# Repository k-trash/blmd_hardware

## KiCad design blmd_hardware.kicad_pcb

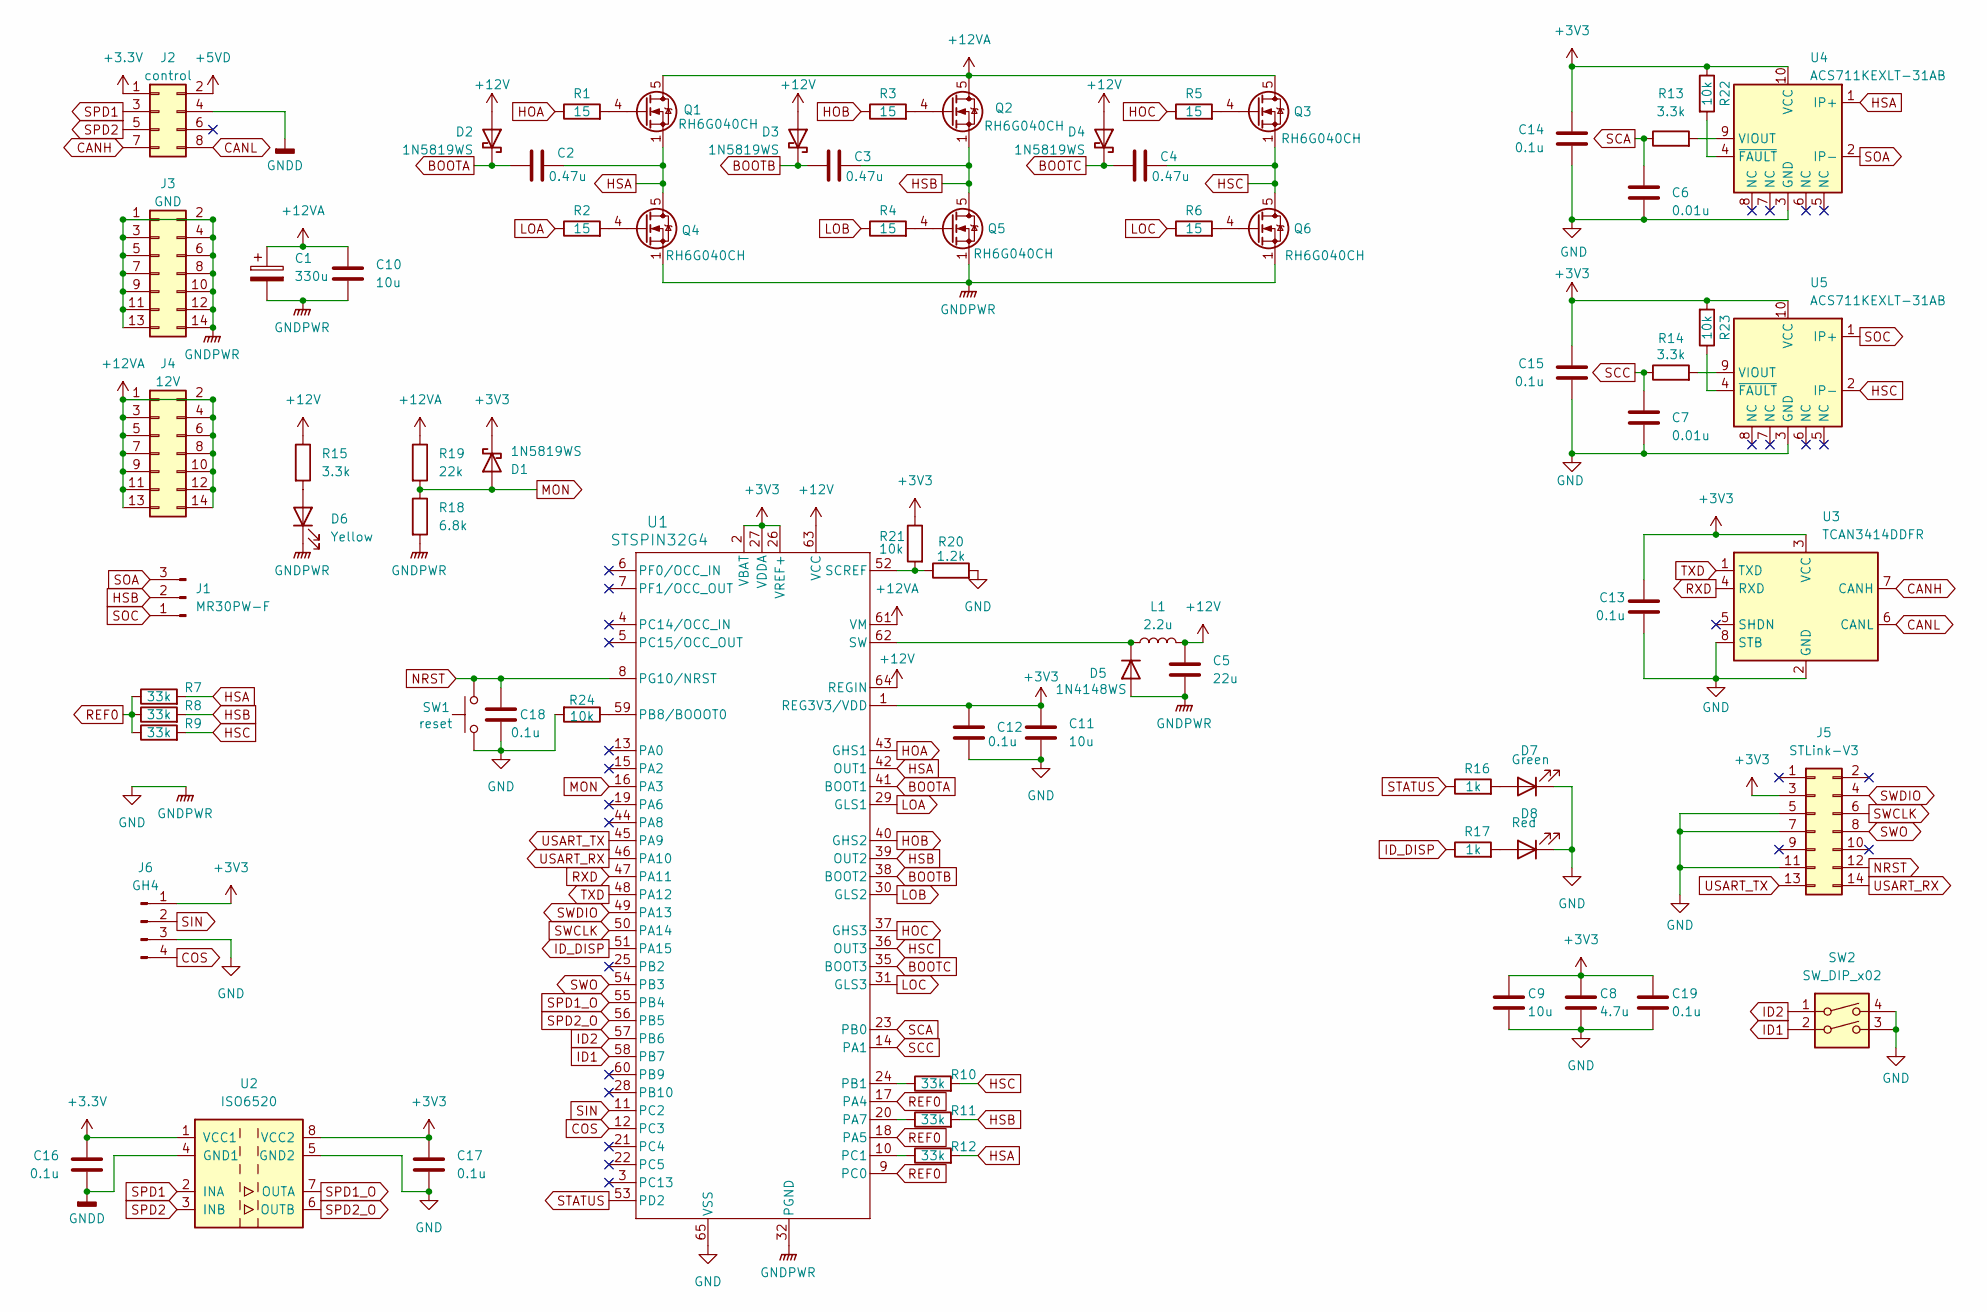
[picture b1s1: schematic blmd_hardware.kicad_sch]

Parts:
C1: 330u; CP_Radial_D10.0mm_P5.00mm
C2, C3, C4: 0.47u; C_0603_1608Metric_Pad1.08x0.95mm_HandSolder
C5: 22u; C_0805_2012Metric_Pad1.18x1.45mm_HandSolder
C6, C7: 0.01u; C_0603_1608Metric_Pad1.08x0.95mm_HandSolder
C8: 4.7u; C_0603_1608Metric_Pad1.08x0.95mm_HandSolder
C9, C10, C11: 10u; C_0603_1608Metric_Pad1.08x0.95mm_HandSolder
C12, C13, C14, C15, C16, C17, C18, C19: 0.1u; C_0603_1608Metric_Pad1.08x0.95mm_HandSolder
D1, D2, D3, D4: 1N5819WS; D_SOD-323_HandSoldering
D5: 1N4148WS; D_SOD-323_HandSoldering
D6: Yellow; LED_0603_1608Metric_Pad1.05x0.95mm_HandSolder
D7: Green; LED_0603_1608Metric_Pad1.05x0.95mm_HandSolder
D8: Red; LED_0603_1608Metric_Pad1.05x0.95mm_HandSolder
J1: MR30PW-F; AMASS_MR30PW-FB_1x03_P3.50mm_Horizontal
J2: control; PinHeader_2x04_P2.54mm_Horizontal
J3: GND; PinHeader_2x07_P2.54mm_Horizontal
J4: 12V; PinHeader_2x07_P2.54mm_Horizontal
J5: STLink-V3; CONN_3220-14-0300-00_CNC
J6: GH4; JST_GH_SM04B-GHS-TB_1x04-1MP_P1.25mm_Horizontal
L1: 2.2u; L_0603_1608Metric_Pad1.05x0.95mm_HandSolder
Q1, Q2, Q3, Q4, Q5, Q6: RH6G040CH; HSMT8
R1, R2, R3, R4, R5, R6: 15; R_0603_1608Metric_Pad0.98x0.95mm_HandSolder
R7, R8, R9, R10, R11, R12: 33k; R_0603_1608Metric_Pad0.98x0.95mm_HandSolder
R13, R14, R15: 3.3k; R_0603_1608Metric_Pad0.98x0.95mm_HandSolder
R16, R17: 1k; R_0603_1608Metric_Pad0.98x0.95mm_HandSolder
R18: 6.8k; R_0603_1608Metric_Pad0.98x0.95mm_HandSolder
R19: 22k; R_0603_1608Metric_Pad0.98x0.95mm_HandSolder
R20: 1.2k; R_0603_1608Metric_Pad0.98x0.95mm_HandSolder
R21, R22, R23, R24: 10k; R_0603_1608Metric_Pad0.98x0.95mm_HandSolder
SW1: reset; RESET
SW2: SW_DIP_x02; SW_DIP_SPSTx02_Slide_Copal_CHS-02B_W7.62mm_P1.27mm
U1: STSPIN32G4; QFN_IN32G4_STM
U2: ISO6520; SOIC-8_3.9x4.9mm_P1.27mm
U3: TCAN3414DDFR; SOT-23-8
U4, U5: ACS711KEXLT-31AB; Allegro_QFN-12-10-1EP_3x3mm_P0.5mm

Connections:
+3.3V: C16.1, J2.1, U2.1 (VCC1)
+3V3: C8.1, C9.1, C11.1, C12.1, C13.1, C14.1, C15.1, C17.1, C19.1, D1.1 (K), J5.3, J6.1, R21.1, R22.1, R23.2, U1.1 (REG3V3/VDD), U1.2 (VBAT), U1.26 (VREF+), U1.27 (VDDA), U2.8 (VCC2), U3.3 (VCC), U4.10 (VCC), U5.10 (VCC)
+5VD: J2.2
+12V: C5.1, D2.2 (A), D3.2 (A), D4.2 (A), L1.2, R15.1, U1.63 (VCC), U1.64 (REGIN)
+12VA: C1.1, C10.1, J4.1, J4.2, J4.3, J4.4, J4.5, J4.6, J4.7, J4.8, J4.9, J4.10, J4.11, J4.12, J4.13, J4.14, Q1.5 (D), Q1.6 (D), Q1.7 (D), Q1.8 (D), Q2.5 (D), Q2.6 (D), Q2.7 (D), Q2.8 (D), Q3.5 (D), Q3.6 (D), Q3.7 (D), Q3.8 (D), R19.1, U1.61 (VM)
BOOTA: C2.2, D2.1 (K), U1.41 (BOOT1)
BOOTB: C3.1, D3.1 (K), U1.38 (BOOT2)
BOOTC: C4.1, D4.1 (K), U1.35 (BOOT3)
CANH: J2.7, U3.7 (CANH)
CANL: J2.8, U3.6 (CANL)
COS: J6.4, U1.12 (PC3)
GND: C1.2, C5.2, C6.2, C7.2, C8.2, C9.2, C10.2, C11.2, C12.2, C13.2, C14.2, C15.2, C17.2, C18.2, C19.2, D5.2 (A), D6.1 (K), D7.1 (K), D8.1 (K), J3.1, J3.2, J3.3, J3.4, J3.5, J3.6, J3.7, J3.8, J3.9, J3.10, J3.11, J3.12, J3.13, J3.14, J5.5, J5.7, J5.11, J6.3, Q4.1 (S), Q4.2 (S), Q4.3 (S), Q5.1 (S), Q5.2 (S), Q5.3 (S), Q6.1 (S), Q6.2 (S), Q6.3 (S), R18.2, R20.2, R24.2, SW1.1, SW2.3, SW2.4, U1.32 (PGND), U1.65 (VSS), U2.5 (GND2), U3.2 (GND), U3.8 (STB), U4.3 (GND), U5.3 (GND)
GNDD: C16.2, J2.4, U2.4 (GND1)
HOA: R1.1, U1.43 (GHS1)
HOB: R3.1, U1.40 (GHS2)
HOC: R5.1, U1.37 (GHS3)
HSA: C2.1, Q1.1 (S), Q1.2 (S), Q1.3 (S), Q4.5 (D), Q4.6 (D), Q4.7 (D), Q4.8 (D), R7.2, R12.2, U1.42 (OUT1), U4.1 (IP+)
HSB: C3.2, J1.2, Q2.1 (S), Q2.2 (S), Q2.3 (S), Q5.5 (D), Q5.6 (D), Q5.7 (D), Q5.8 (D), R8.2, R11.2, U1.39 (OUT2)
HSC: C4.2, Q3.1 (S), Q3.2 (S), Q3.3 (S), Q6.5 (D), Q6.6 (D), Q6.7 (D), Q6.8 (D), R9.2, R10.2, U1.36 (OUT3), U5.2 (IP-)
ID1: SW2.2, U1.58 (PB7)
ID2: SW2.1, U1.57 (PB6)
ID_DISP: R17.1, U1.51 (PA15)
LOA: R2.1, U1.29 (GLS1)
LOB: R4.1, U1.30 (GLS2)
LOC: R6.1, U1.31 (GLS3)
MON: D1.2 (A), R18.1, R19.2, U1.16 (PA3)
NRST: C18.1, J5.12, SW1.2, U1.8 (PG10/NRST)
unnamed: D5.1 (K), L1.1, U1.62 (SW)
unnamed: D6.2 (A), R15.2
unnamed: D7.2 (A), R16.2
unnamed: D8.2 (A), R17.2
unnamed: Q1.4 (G), R1.2
unnamed: Q2.4 (G), R3.2
unnamed: Q3.4 (G), R5.2
unnamed: Q4.4 (G), R2.2
unnamed: Q5.4 (G), R4.2
unnamed: Q6.4 (G), R6.2
unnamed: R11.1, U1.20 (PA7)
unnamed: R10.1, U1.24 (PB1)
unnamed: R24.1, U1.59 (PB8/BOOOT0)
unnamed: R12.1, U1.10 (PC1)
unnamed: R20.1, R21.2, U1.52 (SCREF)
unnamed: R13.2, U4.9 (VIOUT)
unnamed: R22.2, U4.4 (~FAULT)
unnamed: R14.2, U5.9 (VIOUT)
unnamed: R23.1, U5.4 (~FAULT)
REF0: R7.1, R8.1, R9.1, U1.9 (PC0), U1.17 (PA4), U1.18 (PA5)
RXD: U1.47 (PA11), U3.4 (RXD)
SCA: C6.1, R13.1, U1.23 (PB0)
SCC: C7.1, R14.1, U1.14 (PA1)
SIN: J6.2, U1.11 (PC2)
SOA: J1.3, U4.2 (IP-)
SOC: J1.1, U5.1 (IP+)
SPD1: J2.3, U2.2 (INA)
SPD1_O: U1.55 (PB4), U2.7 (OUTA)
SPD2: J2.5, U2.3 (INB)
SPD2_O: U1.56 (PB5), U2.6 (OUTB)
STATUS: R16.1, U1.53 (PD2)
SWCLK: J5.6, U1.50 (PA14)
SWDIO: J5.4, U1.49 (PA13)
SWO: J5.8, U1.54 (PB3)
TXD: U1.48 (PA12), U3.1 (TXD)
USART_RX: J5.14, U1.46 (PA10)
USART_TX: J5.13, U1.45 (PA9)

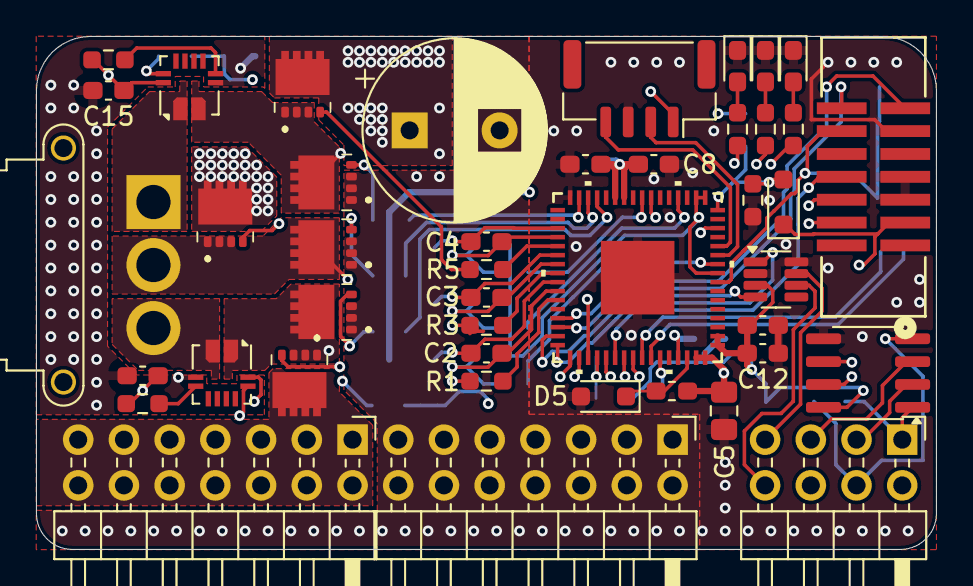
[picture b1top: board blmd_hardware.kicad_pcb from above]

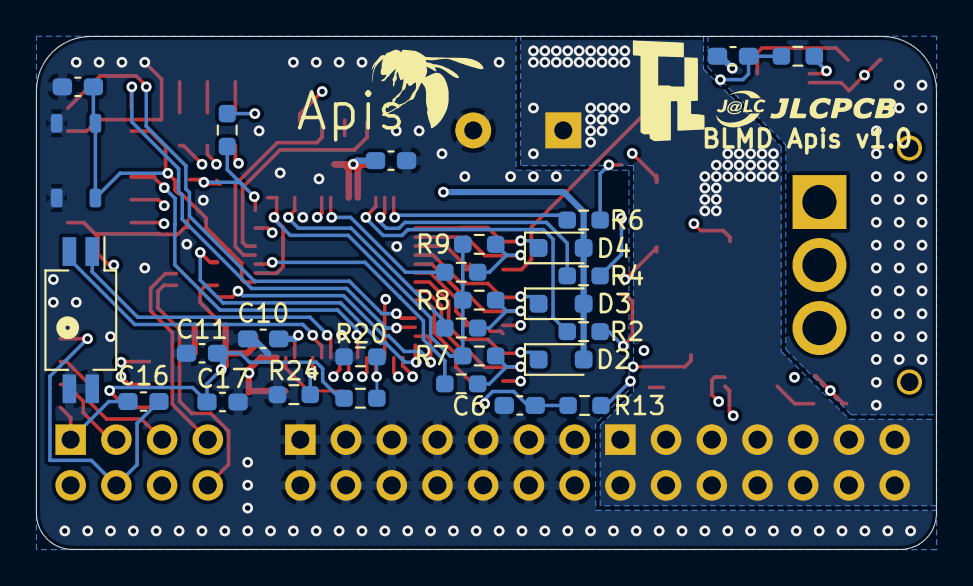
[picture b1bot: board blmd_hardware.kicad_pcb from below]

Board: 4 copper layers, 50.0 x 28.5 mm, 71 parts (28 on the bottom side), 63 nets.

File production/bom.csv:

Designator,Footprint,Quantity,Value,LCSC Part #
C1,CP_Radial_D10.0mm_P5.00mm,1,330u,C106556
C10,0603,1,10u,C76614
"C11, C9",0603,2,10u,C19702
"C12, C13, C14, C15, C16, C17, C18, C19",0603,8,0.1u,C2167395
"C2, C3, C4",0603,3,0.47u,C2176484
C5,0805,1,22u,C45783
"C6, C7",0603,2,0.01u,C19188053
C8,0603,1,4.7u,C19666
"D1, D2, D3, D4",D_SOD-323_HandSoldering,4,1N5819WS,C191023
D5,D_SOD-323_HandSoldering,1,1N4148WS,C2128
D6,0603,1,Yellow,C84268
D7,0603,1,Green,C205450
D8,0603,1,Red,C90692
J1,AMASS_MR30PW-FB_1x03_P3.50mm_Horizontal,1,MR30PW-F,
J2,PinHeader_2x04_P2.54mm_Horizontal,1,control,
J3,PinHeader_2x07_P2.54mm_Horizontal,1,GND,
J4,PinHeader_2x07_P2.54mm_Horizontal,1,12V,
J5,CONN_3220-14-0300-00_CNC,1,STLink-V3,
J6,JST_GH_SM04B-GHS-TB_1x04-1MP_P1.25mm_Horizontal,1,GH4,
L1,0603,1,2.2u,C129931
"Q1, Q2, Q3, Q4, Q5, Q6",HSMT8,6,RH6G040CH,C7049321
"R1, R3, R5",0603,3,15,C22810
"R10, R11, R12, R7, R8, R9",0603,6,33k,
"R13, R14",0603,2,3.3k,
R15,0603,1,3.3k,C22978
"R16, R17",0603,2,1k,C21190
R18,0603,1,6.8k,C23212
R19,0603,1,22k,
"R2, R4, R6",0603,3,15,
R20,0603,1,1.2k,
"R21, R24",0603,2,10k,
"R22, R23",0603,2,10k,C25804
SW1,RESET,1,reset,
SW2,SW_DIP_SPSTx02_Slide_Copal_CHS-02B_W7.62mm_P1.27mm,1,SW_DIP_x02,
U1,QFN_IN32G4_STM,1,STSPIN32G4,
U2,SOIC-8_3.9x4.9mm_P1.27mm,1,ISO6520,
U3,SOT-23-8,1,TCAN3414DDFR,
"U4, U5",Allegro_QFN-12-10-1EP_3x3mm_P0.5mm,2,ACS711KEXLT-31AB,

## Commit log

2024-10-28 temporary place parts
2024-10-28 update gitignore
2024-10-28 remove backup
2024-11-01 complete
2024-11-01 silk complete
2024-11-01 create gerber
2024-11-08 add pdf
2024-11-21 repaterning...
2024-12-08 back up commit
2024-12-08 tmp complete
2025-03-03 fix : vdd vss position
2025-03-05 backup commit
2025-03-12 tmp : complete?
2025-03-17 tmp : schemetic is all over except for can
2025-03-18 tmp : backup commit
2025-03-28 tmp : complete
2025-03-28 create : production file
2025-03-28 change : diode from sod-323f to sod-323
2025-03-28 remove : old gerber files
2025-06-23 fix : emf low path filter
